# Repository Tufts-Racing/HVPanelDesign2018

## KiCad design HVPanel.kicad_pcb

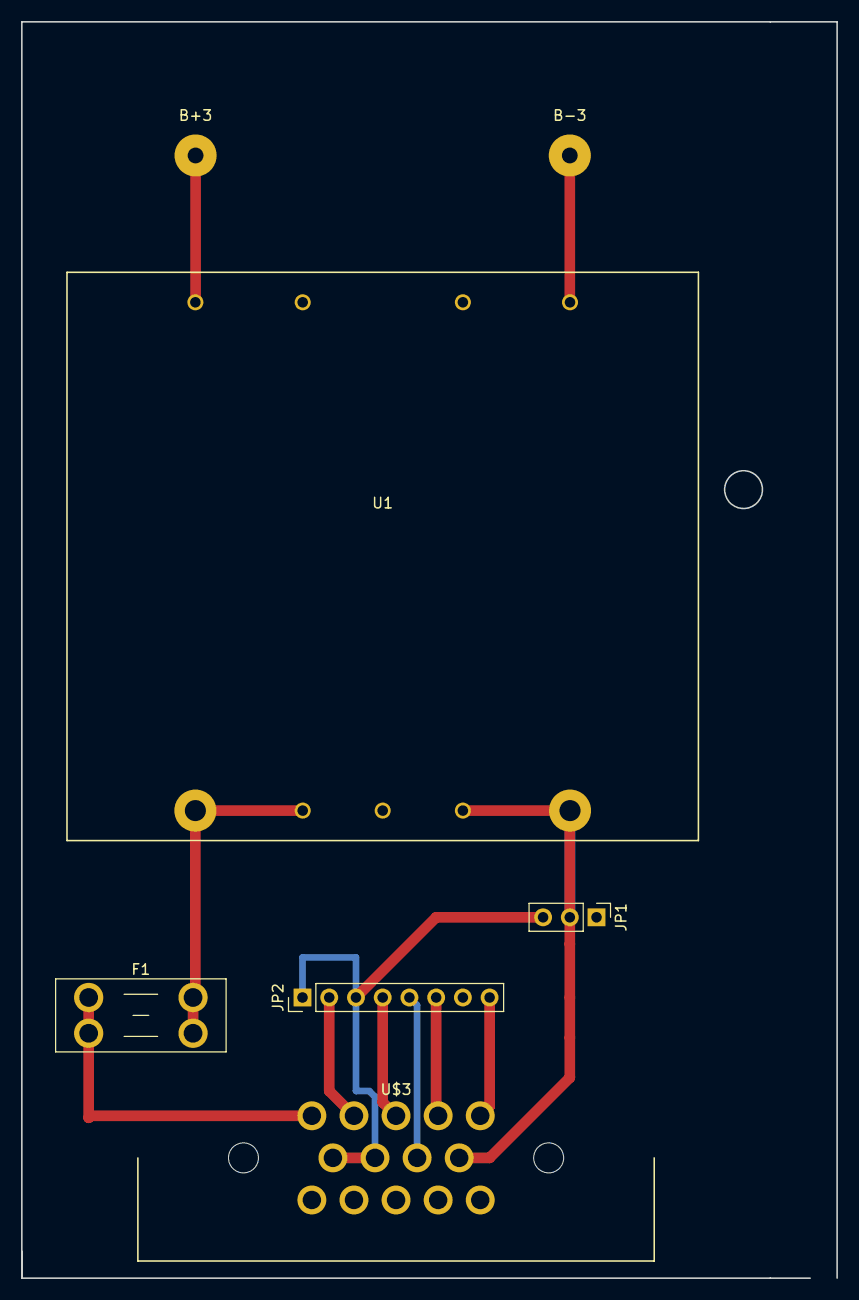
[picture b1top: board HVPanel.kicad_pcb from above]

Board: 2 copper layers, 77.5 x 119.4 mm, 7 parts (0 on the bottom side), 11 nets.

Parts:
B+3: Conn_01x01; SolderWirePad_single_1-5mmDrill
B-3: Conn_01x01; SolderWirePad_single_1-5mmDrill
F1: Fuse; BladeFuse-Mini_Keystone_3568
JP1: Conn_01x03; Pin_Header_Straight_1x03_Pitch2.54mm
JP2: Conn_01x08; Pin_Header_Straight_1x08_Pitch2.54mm
U1: VICOR
U$3: AMPSEAL14; AMP14

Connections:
/CHASSIS_GND2: JP2.4, U$3.3
/D_OUT_HIGH: JP2.5, U$3.8
/D_OUT_LOW: JP2.6, U$3.4
/IMD_FAULT: JP2.8, U$3.5
/IMD_SUPPLY: JP2.2, U$3.2
/TSEL+: F1.1, U$3.1
/TSEL-: JP1.2, U1.8, U1.9, U$3.9
GND: JP1.3, JP2.1, JP2.3, U$3.6, U$3.7
unnamed: B+3.1, U1.1
unnamed: B-3.1, U1.4
unnamed: F1.2, U1.5, U1.6

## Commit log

2017-11-15 added project
2017-12-06 edited schematic, added conections to VICOR
2017-12-11 almost done!
2017-12-11 finished schematic
2018-01-22 started footprint
2018-01-24 more footprint conversion
2018-01-29 deleted resistors, finished footprint
2018-02-19 Almost done with footprint
2018-02-22 Added dimensions
2018-02-26 added hole
2018-02-28 added 4mm hole
